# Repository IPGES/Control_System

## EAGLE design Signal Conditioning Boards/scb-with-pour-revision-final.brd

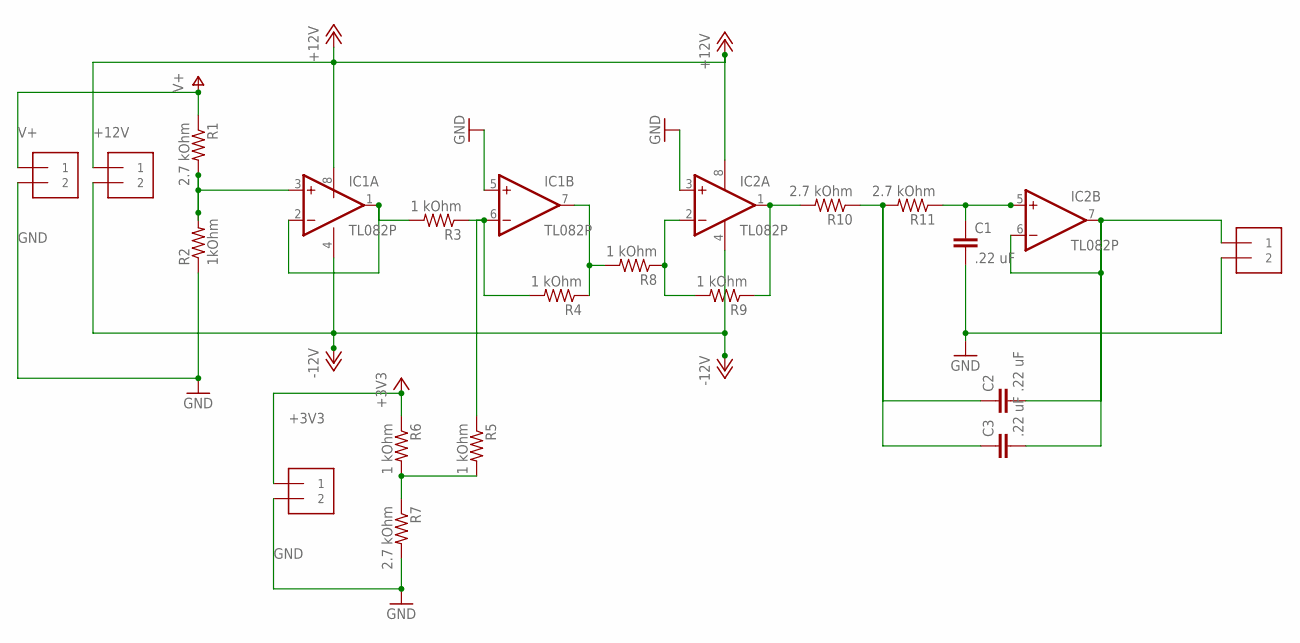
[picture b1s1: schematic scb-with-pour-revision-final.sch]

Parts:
C1, C2, C3: .22 uF; C5B5
IC1, IC2: TL082P; DIL08
J1, J2, J3, J4: 1X2-3.5MM; 3.5MMTERM
R1, R7, R10, R11: 2.7 kOhm; 0207/10
R2: 1kOhm; 0207/10
R3, R4, R5, R6, R8, R9: 1 kOhm; 0207/10

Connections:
+3V3: J2.1, R6.1
+12V: IC1.8 (V+), IC2.8 (V+), J1.1
-12V: IC1.4 (V-), IC2.4 (V-), J1.2
GND: C1.2, IC1.5 (+IN), IC2.3 (+IN), J2.2, J3.2, J4.2, R2.1, R7.2
unnamed: C2.1, C3.1, R10.1, R11.2
unnamed: IC1.1 (OUT), IC1.2 (-IN), R3.2
unnamed: IC1.7 (OUT), R4.1, R8.2
unnamed: IC2.2 (-IN), R8.1, R9.2
unnamed: R5.2, R6.2, R7.1
unnamed: IC2.1 (OUT), R9.1, R10.2
unnamed: C2.2, C3.2, IC2.6 (-IN), IC2.7 (OUT), J4.1
unnamed: C1.1, IC2.5 (+IN), R11.1
unnamed: IC1.6 (-IN), R3.1, R4.2, R5.1
unnamed: IC1.3 (+IN), R1.2, R2.2
V+: J3.1, R1.1

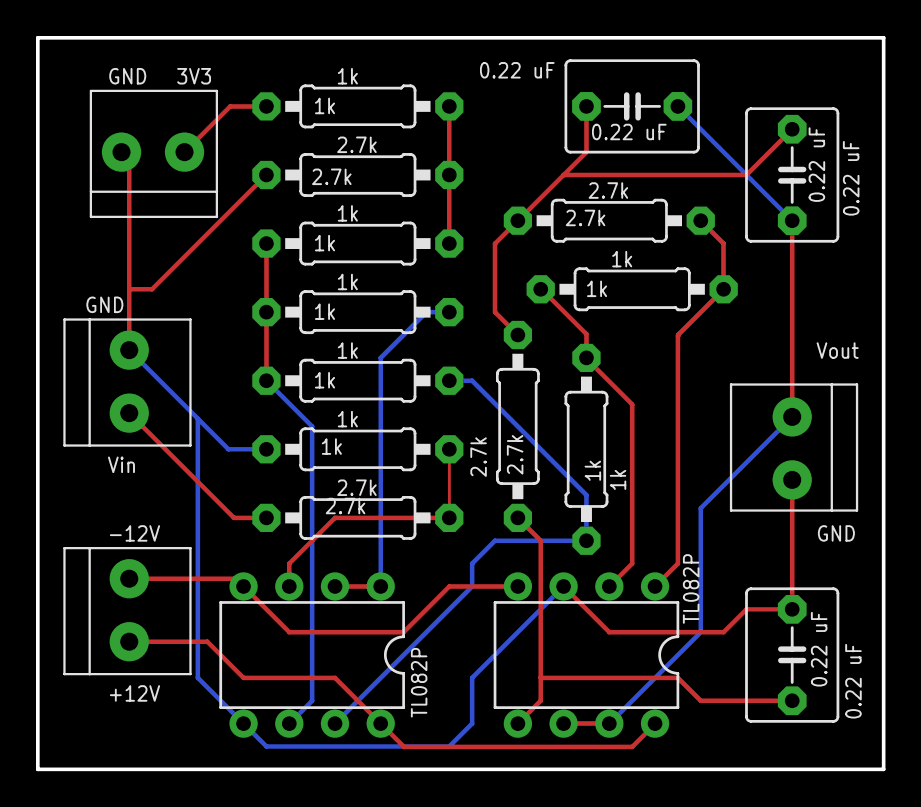
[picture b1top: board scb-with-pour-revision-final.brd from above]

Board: 2 copper layers, 47.0 x 40.6 mm, 20 parts (0 on the bottom side), 15 nets.

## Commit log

2017-11-30 Initial Commit with interpreter, adc, pwm.
2017-12-01 Gate Driver working, did 8mA output on both PB6 and PB7. May have been the problem.
2018-01-28 Add Signal Conditioning Board PCB files
2018-01-31 FIxed Priority Problems.
2018-02-13 Added timing to adc
2018-02-13 Peak to Peak
2018-02-15 Auto stash before merge of "master" and "origin/master"
2018-02-19 Freq Reading
2018-02-19 Add Heap.c
2018-02-19 Range Calculation
2018-02-19 Freq Function
2018-02-19 Julia Control System
2018-02-19 Controls.h
2018-02-19 stuff
2018-02-21 Julia may or may not be correct
2018-02-21 Jim Random
2018-02-21 Restore to production.
2018-02-21 Build Logs
2018-02-21 Controls Thread
2018-03-05 Fixed syntax error control.c
2018-03-05 updated gitignore
2018-03-05 Added PWM. 3 total.
2018-03-05 Added python controls for wind/solar simulation on TM4C
2018-03-05 Reverted Old Interpreter
2018-03-05 Reverted Old Interpreter 2
2018-03-05 GPIO
2018-03-05 Added duty cycle functionality for load. Successfully simulates load/wind data for a day. New test file takes in input for load (and wind/solar)
2018-03-07 Added subplots for all curves.
2018-03-07 Solar Wind Load excel files
2018-03-09 Formatting
2018-03-09 Demo.htm
2018-03-09 SPI 128
2018-03-09 SPI works
2018-03-13 Add a gitignore with common unneeded Keil files
2018-03-18 gitignore is now working, thanks Kassi
2018-03-18 PWM refactor.
2018-03-18 Refactor PMW part of interpreter.
2018-03-18 Refactor GPIO and Wind PWM
2018-03-18 Moved Python Script. PWM support 100. Wind 0% doesn't work.
2018-03-18 Refactor Interpreter to take SPI commands.
2018-03-18 Added back in RMS
2018-03-19 Added write SPI to tm4c
2018-03-19 Got rid of ADC print.
2018-03-19 Braden wrote stuff.
2018-03-19 added solar/wind output thread program (haven't tested yet)
2018-03-21 first stab at multithreading toCloud and PWM write program
2018-03-21 Added threading for reading/writing from/to the TM4C. Need to implement semaphores, but works more or less.
2018-03-21 Added a lock solution before I forget
2018-03-22 VRMS voltage, need testing for other duty cycle
2018-03-22 Working.
2018-03-22 8 ADC inputs.
2018-03-24 New 8ADC Maybe doesn't work
2018-03-24 Load VRMS reads!
2018-03-24 Calibration Data
2018-03-26 Threading working but too slow to actually be useful. Just using two TM4C's instead
2018-03-28 HI Braden
2018-03-28 Wind/Load/PV all working
2018-04-04 Ben Day
2018-04-08 Santoso Day
2018-04-08 Added get functions for sensor readings and linear regression sensor
2018-04-11 Controls
2018-04-11 Breaker
2018-04-11 Revert "Breaker"
    This reverts commit c82fe8f27750904cdec05e3661ef6e4eb769eb2c.
2018-04-11 Revert "?"
    This reverts commit 09d780577c2a8ca740b0f4999f6fa2516808f85a.
2018-04-11 Git Problems
2018-04-11 Fixed Bug
2018-04-12 Updated S/W/L plot for real output; added breaker testing file
2018-04-16 Revert "a"
    This reverts commit f5166843b71052e9ddde631c0bda2b525a24a86c.
2018-04-16 Final Working
2018-04-16 Revert "Al"
    This reverts commit 8f9a78c19f5546e98667026480c70c36b1fe1e3e.
2018-04-17 Bro-Science Talk
